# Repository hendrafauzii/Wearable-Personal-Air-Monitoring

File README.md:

# Wearable Personal Air Monitoring

## Daftar Isi
 - [Daftar Isi](#Daftar-isi)  
 - [Deskripsi](#Deskripsi) 
 - [Library Depedency](#Library-depedency)
 - [PCB Design](#PCB-Design) 
 - [Bill of Materials](#BOMs) 
 - [Dashboard](#dasboard-pada-platform-iot-xl-axiata-flex-iot)
 - [Galeri](#Galeri)

## Deskripsi
Perangkat ini dirancang pada tahun 2019 yang dibuat menyerupai sebuah jam tangan bagi penderita sinusitis yang sensitif terhadap perubahan udara. Terdapat beberapa sensor yang digunakan diantaranya  sensor BME280 sebagai pengukuran suhu, kelembapan, dan tekanan udara secara real time, dan MAX30105 sebagai sensor tambahan yang berfungsi untuk mengukur detak jantung. Alat ini akan memberikan notifikasi ketika kondisi udara tidak ideal bagi penderita sinusitis.

## Library Depedency
Perangkat ini diprogram menggunakan ArduinoIDE yang berbasis C/C++, dengan memilih ESP32 Dev Module pada bagian board di ArduinoIDE.
Adapun library depedency yang digunakan diantaranya :

**• Adafruit Sensor** https://github.com/adafruit/Adafruit_Sensor

**• BME280** https://downloads.arduino.cc/libraries/github.com/adafruit/Adafruit_BME280_Library-1.1.0.zip

**• MAX3010x** https://github.com/sparkfun/SparkFun_MAX3010x_Sensor_Library

**• SSD1306 Display** https://github.com/ThingPulse/esp8266-oled-ssd1306

**• PubSub Client** https://github.com/knolleary/pubsubclient

**• ArduinoJson v5** https://github.com/bblanchon/ArduinoJson/tree/5.x

## PCB Design

## BOMs
**• Bagian Atas**
No | Parts          | Value       | Package                  | Qty 
-- | -------------- | ----------- | ------------------------ | --- |
1  | LED1           | LED         | CHIPLED_0805             |  1  |
2  | SV1	           | MA05        | MA05-2	                  |  1  |
3  | JP1            | PIN HEAD    | 1X06/90                  |  1  |
4  | U$3, U$4       | SIDE SWITCH | SIDE_SWITCH              |  2  |
5  | R1, R2, R4, R5 | 10K	        | R0805                    |  4  |
6  | R3	            | 1K	         | R0805                    |  1  |
7  | U$1	           | BME280	     | BME280                   |	 1  |
8  | OLED-DISPLAY   | OLED-128X64 | 128X64-I2C               |	 1  |
9  | U1	            | ESP32	      | ESP32-WROOM              |  1  |
10 | J1	            | MICRO USB	  | GCT_USB3065-XX-00-A_REVE |  1  |
11 | Q1, Q2	        | MMBT2222A	  | SOT23                    |  2  |
12 | X1	            | POWER       | B2B-PH-SM4-TB            |  1  |
13 | U$2	           | SWITCH	     | MSK-12C02                |  1  |

**• Bagian Bawah**
No | Parts              | Value    | Package          | Qty 
-- | ------------------ | -------- | ---------------- | --- |
1  | CHRG, STBY	        | LED      | CHIPLED_0805     |	 2  |
2  | MAX30100	          | MAX30100 |	MA04-1           |	 1  |
3  | SV1                | MA05-2   |	MA05-2           |	 1  |
4  | 0 (Not Used)       | 0        |	R0805            |	 1  |
5  | R1, R2, R3, R4, R8 | 10K      |	R0805            |	 5  |
6  | C1, C2, C3         | 10uF     |	C0805            |  3  |
7  | R5, R6             | 1K       |	R0805            |  2  |
8  | C4                 | 1uF      |	C0805            |  1  |
9  | R7                 | 2K       |	R0805            |  1  |
10 | U2                 | AP2112K  |	SOT95P285X140-5N |  1  |
11 | S1                 |	BUT1     |	SIDE_SWITCH      |  1  |
12 | S2                 |	BUT2     |	SIDE_SWITCH	     |  1  |
13 | S3                 |	BUT3     |	SIDE_SWITCH	     |  1  |
14 | S4                 |	BUT4     |	SIDE_SWITCH	     |  1  |
15 | IC1                |	TP4056   |	SOP-8	           |  1  |

## Dasboard pada Platform IoT XL Axiata (Flex-IoT)
Perangkat ini dihubungkan dengan Platform IoT XL Axiata [(Flex-IoT)](https://portal.flexiot.xl.co.id/) menggunakan WiFi dengan Protokol MQTT, sehingga dapat dibuat dashboard untuk monitoring seperti yang terlihat pada gambar berikut. 

## Galeri
No |  Gambar                                                                                                                     | Keterangan         
-- |  -------------------------------------------------------------------------------------------------------------------------- | ------------------------- |
1  |   | Menghubungkan ke WiFi     |
2  |   |	Menghubungkan dengan MQTT |
3  |   |	Tampilan utama berupa suhu lingkungan sekitar,      kelembapan udara, dan jam digital.          |
4  |   | Slide kedua merupakan ***altitude*** atau ketinggian dari permukaan bumi.     |
5  |   |	Slide ketiga merupakan tekanan udara sekitar. |
6  |   |	Pengaturan zona wktu dan batas suhu maksimal dan minimum |

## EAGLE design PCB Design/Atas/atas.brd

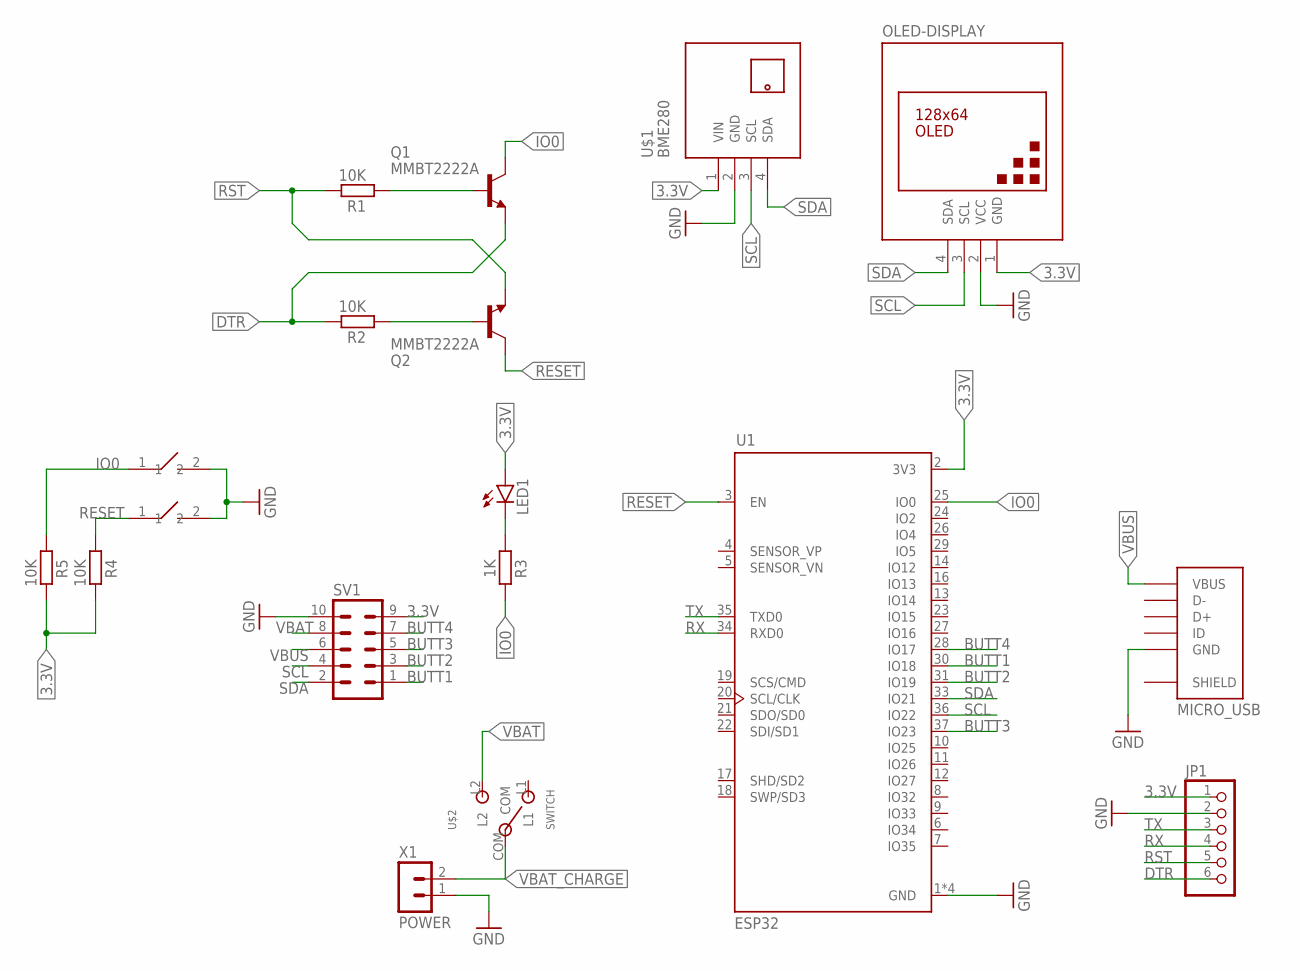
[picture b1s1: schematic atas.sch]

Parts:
J1: MICRO_USB; GCT_USB3065-XX-00-A_REVE
JP1: PINHD-1X6/90; 1X06/90
LED1: LEDCHIPLED_0805; CHIPLED_0805
OLED-DISPLAY: DISPLAY-OLED-128X64-I2C
Q1, Q2: MMBT2222A; SOT23
R1, R2, R4, R5: 10K; R0805
R3: 1K; R0805
SV1: MA05-2
U1: ESP32; MODULE_ESP32-WROOM-32D
U$1: BME280; TEMP-HUM-PRES-BME280
U$2: SWITCH; MSK-12C02
U$3, U$4: SIDE_SWITCH
X1: POWER; B2B-PH-SM4-TB

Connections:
3.3V: JP1.1, LED1.A, OLED-DISPLAY.1 (GND), R4.2, R5.2, SV1.9, U1.2 (3V3), U$1.1 (VIN)
BUTT1: SV1.1, U1.30 (IO18)
BUTT2: SV1.3, U1.31 (IO19)
BUTT3: SV1.5, U1.37 (IO23)
BUTT4: SV1.7, U1.28 (IO17)
DTR: JP1.6, Q1.2 (E), R2.2
GND: J1.5 (GND), JP1.2, OLED-DISPLAY.2 (VCC), SV1.10, U1.1 (GND), U1.15 (GND), U1.38 (GND), U1.39 (GND), U$1.2 (GND), U$3.2 (1), U$4.2 (1), X1.1
IO0: Q1.3 (C), R3.2, R5.1, U1.25 (IO0), U$3.1 (2)
unnamed: Q1.1 (B), R1.1
unnamed: Q2.1 (B), R2.1
unnamed: LED1.C, R3.1
RESET: Q2.3 (C), R4.1, U1.3 (EN), U$4.1 (2)
RST: JP1.5, Q2.2 (E), R1.2
RX: JP1.4, U1.34 (RXD0)
SCL: OLED-DISPLAY.3 (SCL), SV1.4, U1.36 (IO22), U$1.3 (SCL)
SDA: OLED-DISPLAY.4 (SDA), SV1.2, U1.33 (IO21), U$1.4 (SDA)
SHIELD: J1.6 (SHIELD), J1.7 (SHIELD), J1.8 (SHIELD), J1.9 (SHIELD)
TX: JP1.3, U1.35 (TXD0)
VBAT: SV1.8, U$2.L2
VBAT_CHARGE: U$2.COM, X1.2
VBUS: J1.1 (VBUS), SV1.6

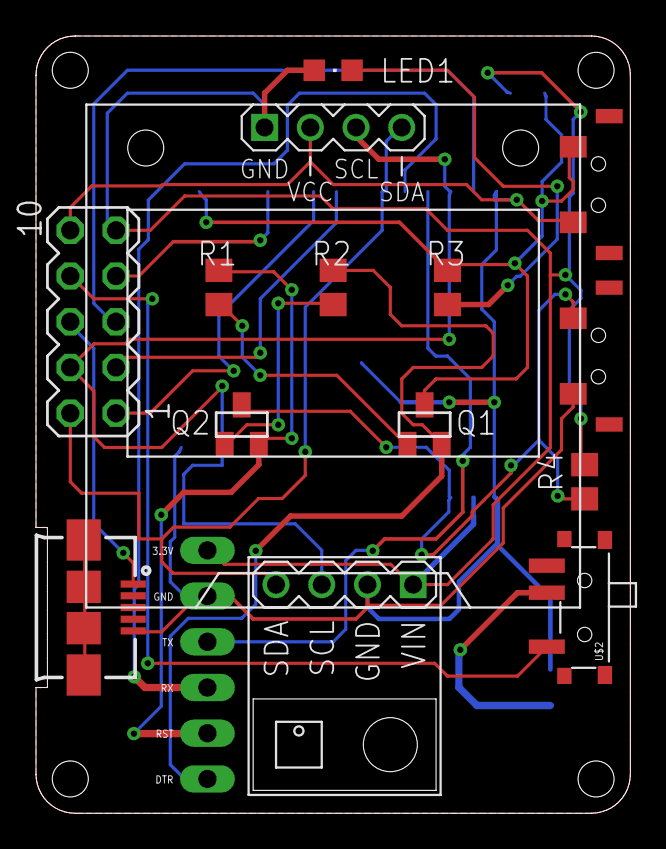
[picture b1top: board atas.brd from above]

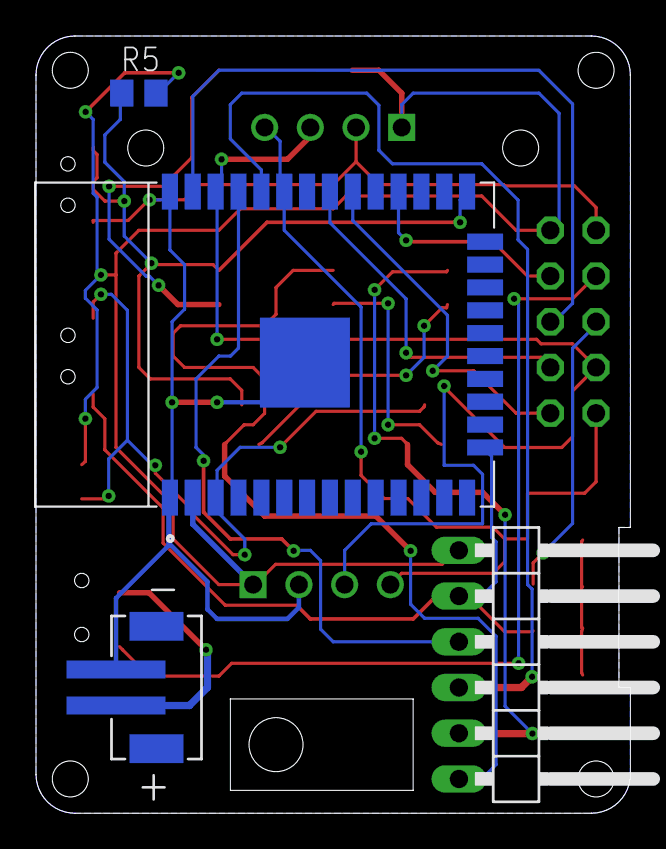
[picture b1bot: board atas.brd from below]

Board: 2 copper layers, 33.0 x 43.2 mm, 18 parts (4 on the bottom side), 21 nets.

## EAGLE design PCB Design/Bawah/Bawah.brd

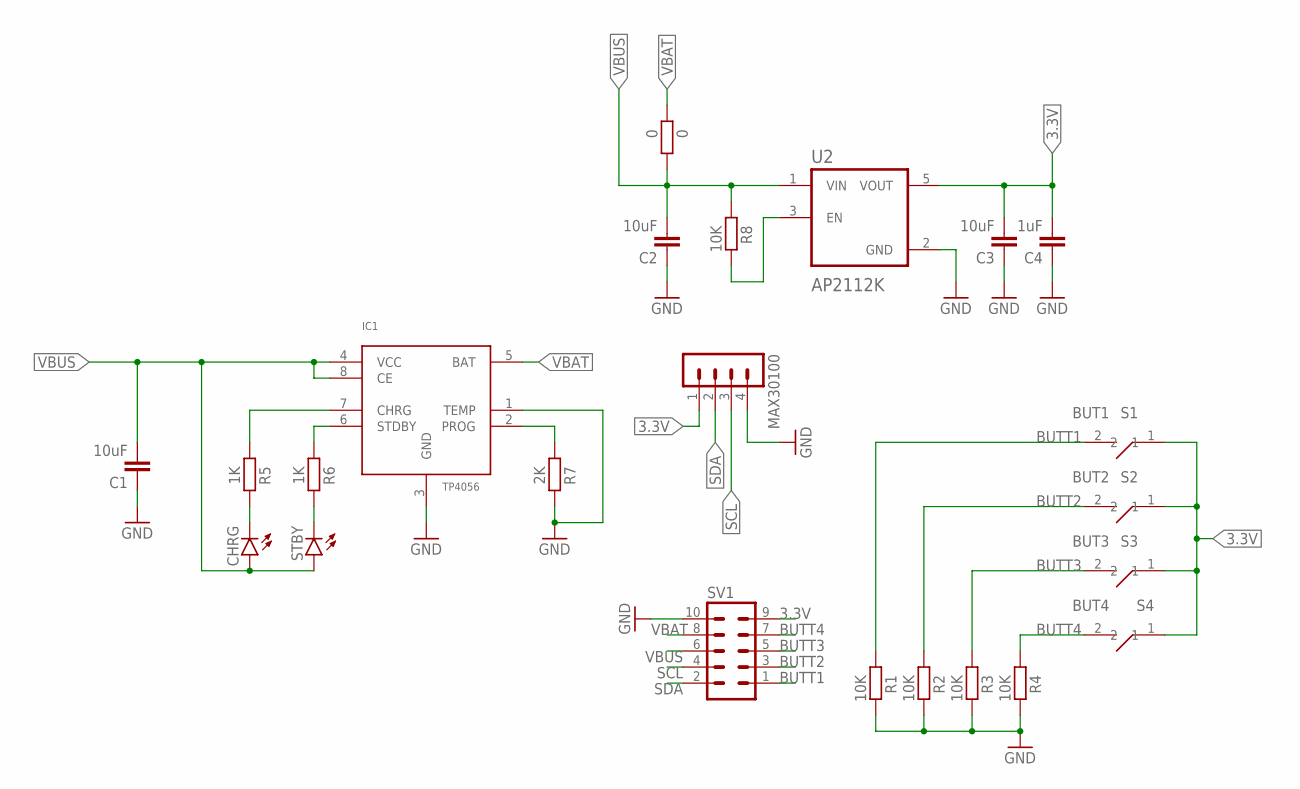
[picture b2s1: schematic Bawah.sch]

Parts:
0: 0; R0805
C1, C2, C3: 10uF; C0805
C4: 1uF; C0805
CHRG: LEDCHIPLED_0805; CHIPLED_0805
IC1: TP4056; SOP-8
MAX30100: MA04-1
R1, R2, R3, R4, R8: 10K; R0805
R5, R6: 1K; R0805
R7: 2K; R0805
S1: BUT1; SIDE_SWITCH
S2: BUT2; SIDE_SWITCH
S3: BUT3; SIDE_SWITCH
S4: BUT4; SIDE_SWITCH
STBY: LEDCHIPLED_0805; CHIPLED_0805
SV1: MA05-2
U2: AP2112K; SOT95P285X140-5N

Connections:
3.3V: C3.2, C4.2, MAX30100.1, S1.1 (2), S2.1 (2), S3.1 (2), S4.1 (2), SV1.9, U2.5 (VOUT)
BUTT1: R1.1, S1.2 (1), SV1.1
BUTT2: R2.1, S2.2 (1), SV1.3
BUTT3: R3.1, S3.2 (1), SV1.5
BUTT4: R4.1, S4.2 (1), SV1.7
GND: C1.1, C2.1, C3.1, C4.1, IC1.1 (TEMP), IC1.3 (GND), MAX30100.4, R1.2, R2.2, R3.2, R4.2, R7.2, SV1.10, U2.2 (GND)
unnamed: IC1.6 (STDBY), R6.1
unnamed: R8.2, U2.3 (EN)
unnamed: IC1.7 (CHRG), R5.1
unnamed: CHRG.C, R5.2
unnamed: R6.2, STBY.C
unnamed: IC1.2 (PROG), R7.1
SCL: MAX30100.3, SV1.4
SDA: MAX30100.2, SV1.2
VBAT: 0.1, IC1.5 (BAT), SV1.8
VBUS: 0.2, C1.2, C2.2, CHRG.A, IC1.4 (VCC), IC1.8 (CE), R8.1, STBY.A, SV1.6, U2.1 (VIN)

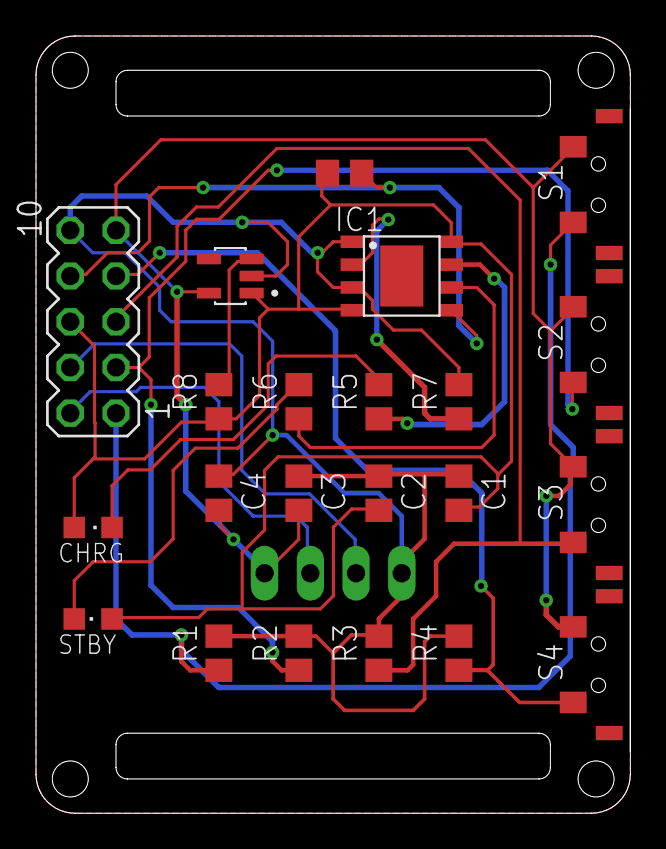
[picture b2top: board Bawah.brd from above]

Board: 2 copper layers, 33.0 x 43.2 mm, 23 parts (1 on the bottom side), 16 nets.

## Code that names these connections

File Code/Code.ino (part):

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#define I2C_SCL 22
#define BME280_ADD 0x76
#define OLED_ADD 0x3c
#define butt1 18
#define butt2 19
#define butt3 23
#define butt4 17

/*
 * Configure MQTT
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  client.setServer(mqtt_server, 1883);
  client.setCallback(callback);
  
  pinMode(butt1, INPUT);
  pinMode(butt2, INPUT);
  pinMode(butt3, INPUT);
  pinMode(butt4, INPUT);
  delay(100);
  
  startMillis = millis();
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
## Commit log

2021-08-21 Create Newfolder
2021-08-21 Add main code
2021-08-21 Add PCB design

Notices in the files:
parts and their libraries:
diy-modules: Released under the Creative Commons Attribution 4.0 International License: http://creativecommons.org/licenses/by/4.0
